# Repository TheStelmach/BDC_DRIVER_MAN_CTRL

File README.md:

# BDC_DRIVER_V2.0-MC
Simple brushed motor controller based on Timer 555

The board features two push buttons and two 20k variable resistors, for regulated bi-directional PWM control of a brushless DC motor.
MAX VOLTAGE: 5V
MAX CURRENT: 1A

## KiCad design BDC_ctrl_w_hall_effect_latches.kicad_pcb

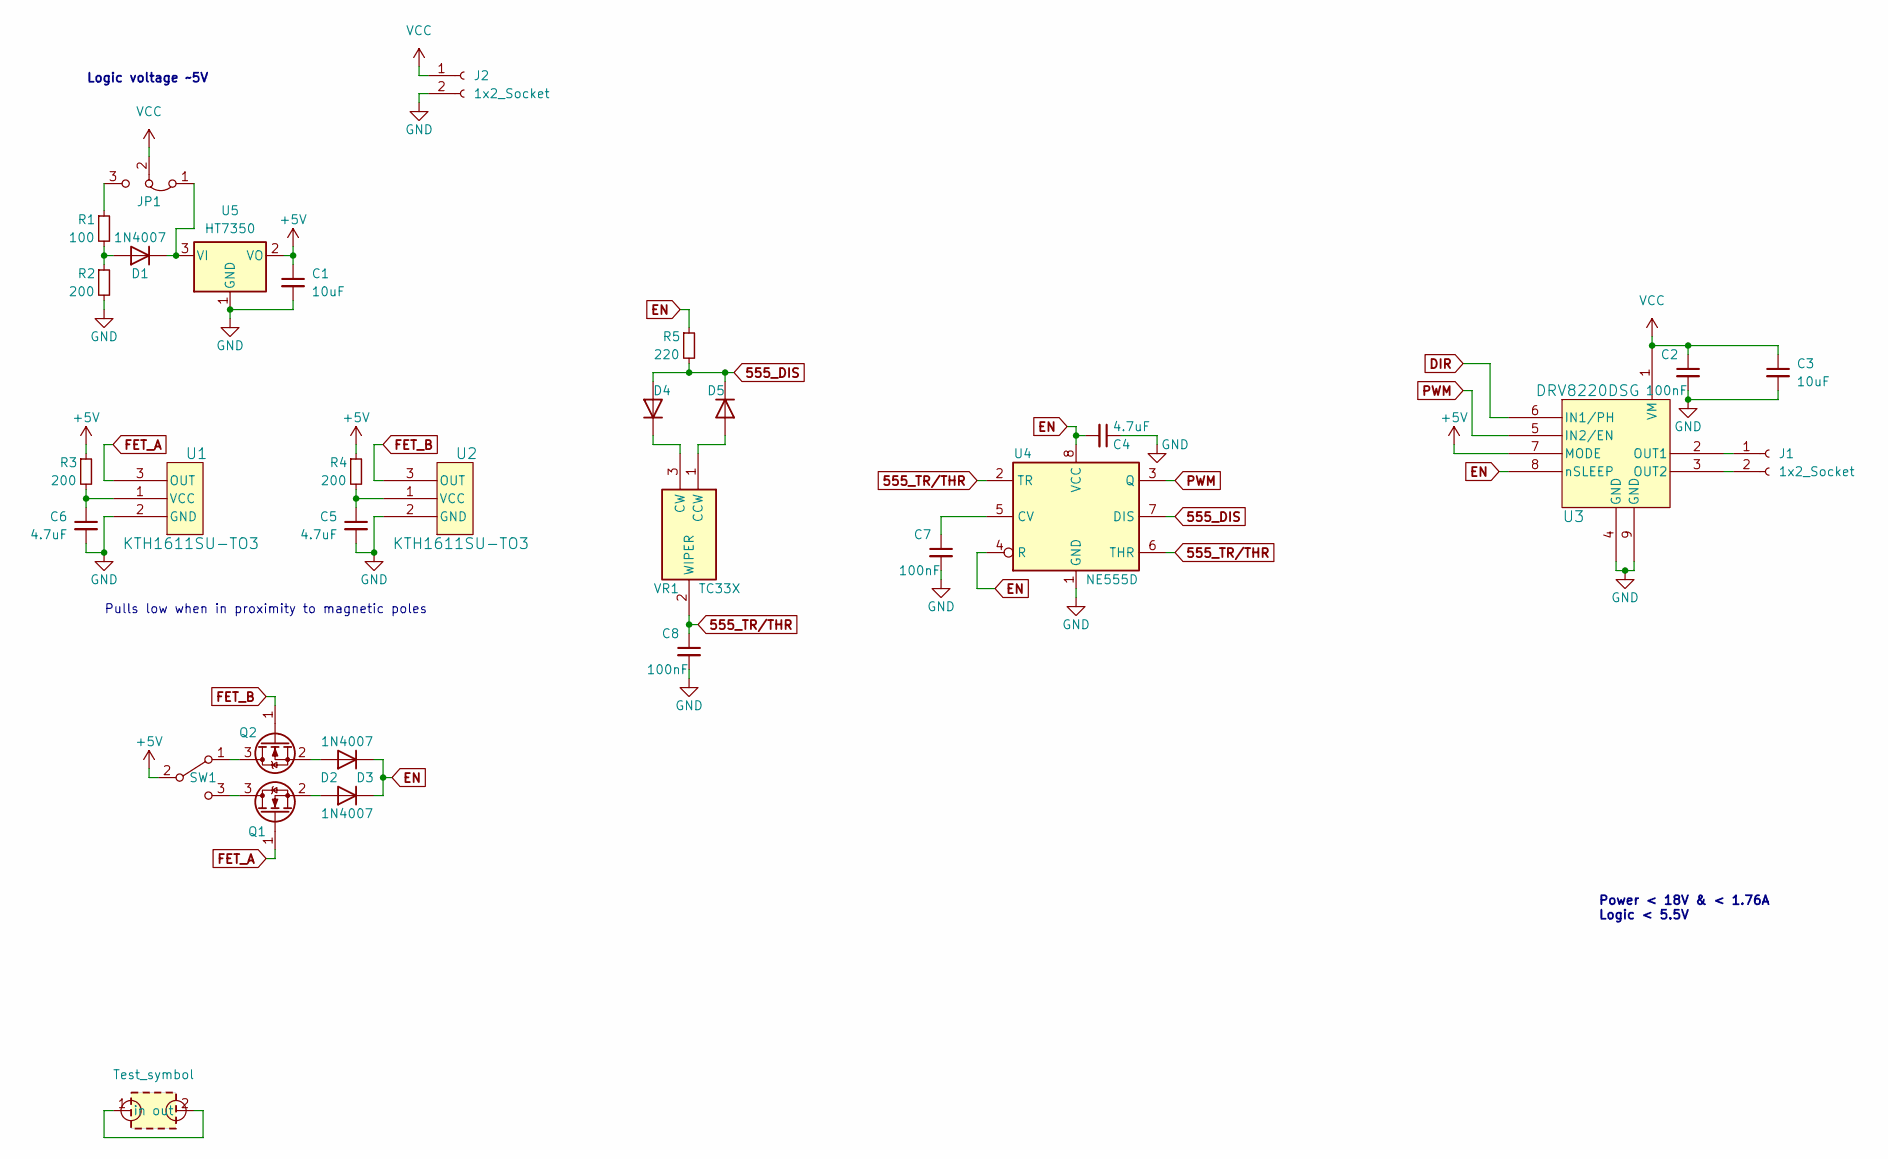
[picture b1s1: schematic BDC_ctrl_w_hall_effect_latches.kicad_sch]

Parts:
C1, C3: 10uF; C_1206_3216Metric_Pad1.33x1.80mm_HandSolder
C2, C7, C8: 100nF; C_0603_1608Metric_Pad1.08x0.95mm_HandSolder
C4, C5, C6: 4.7uF; C_0603_1608Metric_Pad1.08x0.95mm_HandSolder
D1, D2, D3, D4, D5: 1N4007; D_SOD-123F
J1, J2: 1x2_Socket; JST_XH_B2B-XH-A_1x02_P2.50mm_Vertical
JP1: Jumper_3_Bridged12; PinHeader_1x03_P2.54mm_Vertical
Q1, Q2: 2N7002K; SOT-23
R1: 100; R_0603_1608Metric_Pad0.98x0.95mm_HandSolder
R2, R3, R4: 200; R_0603_1608Metric_Pad0.98x0.95mm_HandSolder
R5: 220; R_0603_1608Metric_Pad0.98x0.95mm_HandSolder
SW1: SW_SPDT; SW_SPDT_PCM12
Test_symbol: (no value)
U1, U2: KTH1611SU-TO3; TO-92Flat
U3: DRV8220DSG; WSON-8-1EP_2x2mm_P0.5mm_EP0.9x1.6mm_ThermalVias
U4: NE555D; SOIC-8_3.9x4.9mm_P1.27mm
U5: HT7350; SOT-23_Handsoldering
VR1: TC33X; Potentiometer_Bourns_TC33X_Vertical; Mouser Part Number 652-TC33X-2-303E

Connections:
555_DIS: D4.2 (A), D5.1 (K), R5.2, U4.7 (DIS)
555_TR/THR: C8.1, U4.2 (TR), U4.6 (THR), VR1.2 (WIPER)
+5V: C1.1, R3.1, R4.1, SW1.2 (B), U3.7 (MODE), U5.2 (VO)
DIR: U3.6 (IN1/PH)
EN: C4.2, D2.1 (K), D3.1 (K), R5.1, U3.8 (nSLEEP), U4.4 (R), U4.8 (VCC)
FET_A: Q1.1 (G), U1.3 (OUT)
FET_B: Q2.1 (G), U2.3 (OUT)
GND: C1.2, C2.2, C3.2, C4.1, C5.2, C6.2, C7.2, C8.2, J2.2, R2.2, U1.2 (GND), U2.2 (GND), U3.4 (GND), U3.9 (GND), U4.1 (GND), U5.1 (GND)
unnamed: D1.2 (A), R1.2, R2.1
unnamed: D1.1 (K), JP1.1 (A), U5.3 (VI)
unnamed: D2.2 (A), Q2.2 (S)
unnamed: D3.2 (A), Q1.2 (S)
unnamed: D4.1 (K), VR1.3 (CW)
unnamed: D5.2 (A), VR1.1 (CCW)
unnamed: J1.1, U3.2 (OUT1)
unnamed: J1.2, U3.3 (OUT2)
unnamed: JP1.3 (B), R1.1
unnamed: Q1.3 (D), SW1.3 (C)
unnamed: Q2.3 (D), SW1.1 (A)
unnamed: Test_symbol.1 (in), Test_symbol.2 (out)
unnamed: C6.1, R3.2, U1.1 (VCC)
unnamed: C5.1, R4.2, U2.1 (VCC)
unnamed: C7.1, U4.5 (CV)
PWM: U3.5 (IN2/EN), U4.3 (Q)
VCC: C2.1, C3.1, J2.1, JP1.2 (C), U3.1 (VM)

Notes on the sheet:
Power < 18V & < 1.76A Logic < 5.5V
Pulls low when in proximity to magnetic poles
Logic voltage ~5V

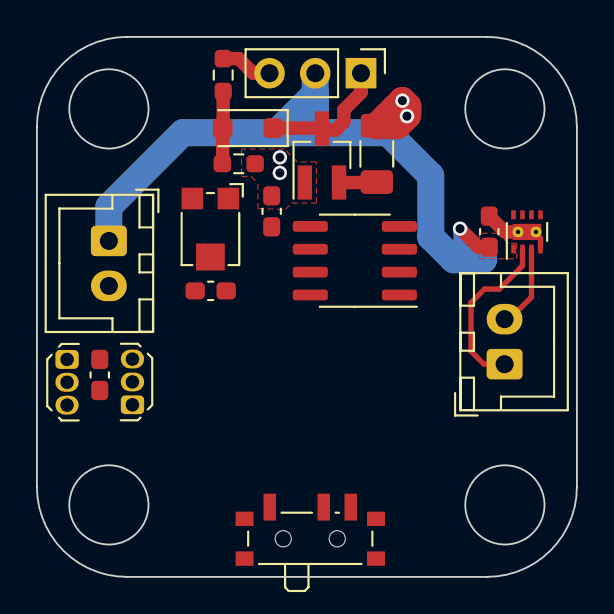
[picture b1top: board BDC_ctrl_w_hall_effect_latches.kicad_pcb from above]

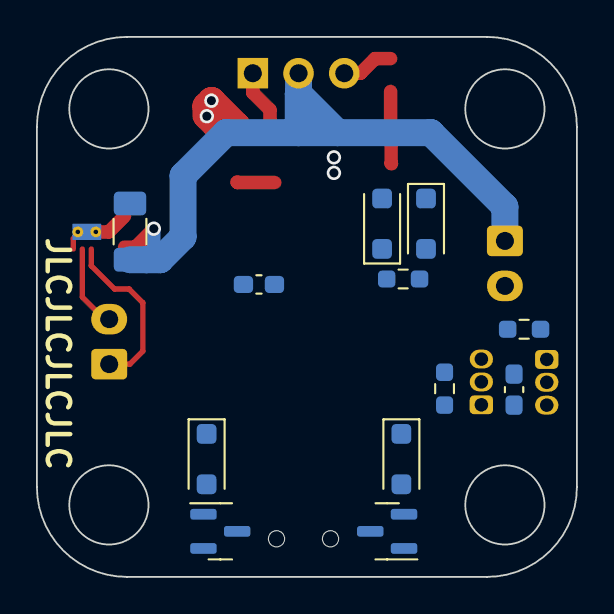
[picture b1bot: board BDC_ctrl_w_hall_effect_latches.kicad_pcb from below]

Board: 2 copper layers, 30.0 x 30.0 mm, 30 parts (12 on the bottom side), 23 nets.

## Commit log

2024-01-11 Add files via upload
    Version 2, currently unfinished. Design is more efficient and an H-bridge chip by TI is used instead of regular H-bridge circuit.
2024-01-11 Add files via upload
    Version 2, currently incomplete. More efficient power conversion and overvoltage protection. An H-bridge chip by TI used instead of a regular H-bridge circuit for space considerations.
